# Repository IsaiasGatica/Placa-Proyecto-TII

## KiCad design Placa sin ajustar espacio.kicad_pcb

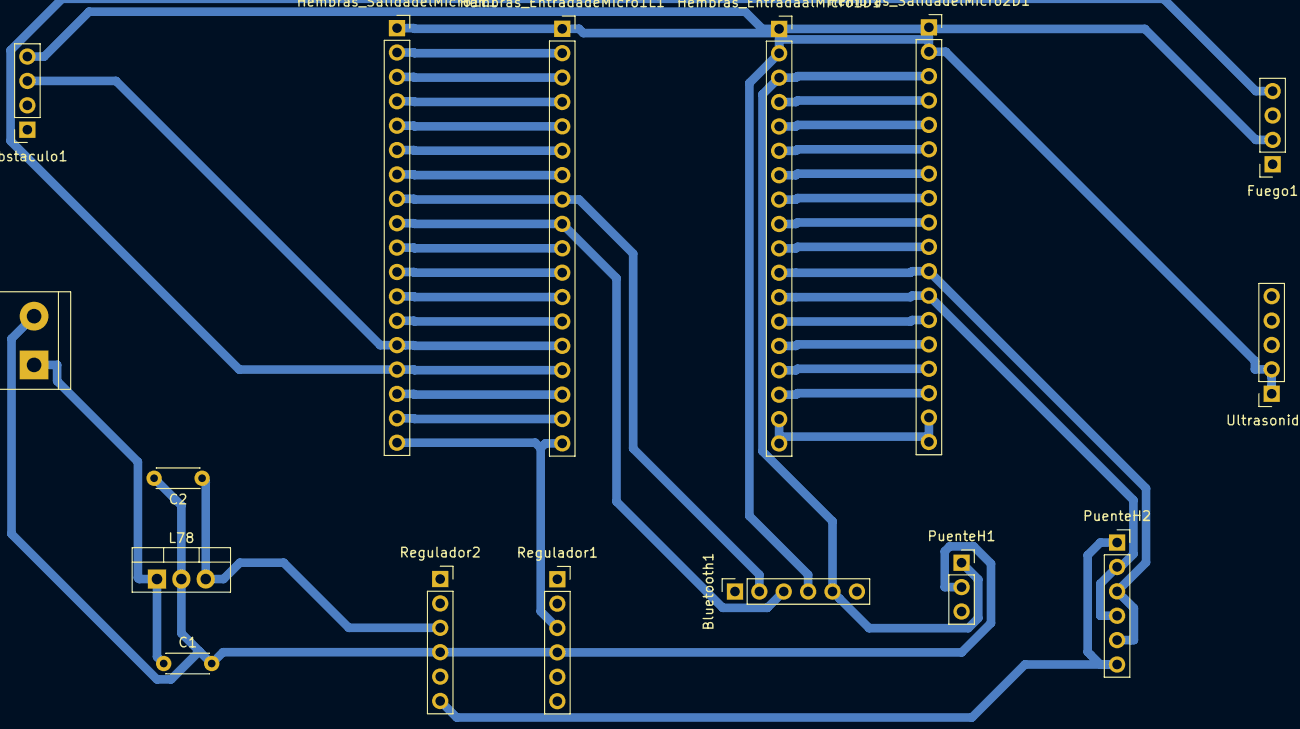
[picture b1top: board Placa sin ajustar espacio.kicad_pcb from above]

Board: 2 copper layers, 20 parts (0 on the bottom side), 34 nets.

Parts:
Alimentacion1: Screw_Terminal_01x02; TerminalBlock_bornier-2_P5.08mm
Bluetooth1: Conn_01x06_Female; PinSocket_1x06_P2.54mm_Vertical
C1: 224; C_Disc_D4.3mm_W1.9mm_P5.00mm
C2: 104; C_Disc_D4.3mm_W1.9mm_P5.00mm
Fuego1: Conn_01x04_Female; PinSocket_1x04_P2.54mm_Vertical
Hembras_EntradaalMicro1D1: Conn_01x18_Female; PinSocket_1x18_P2.54mm_Vertical
Hembras_EntradadeMicro1L1: Conn_01x18_Female; PinSocket_1x18_P2.54mm_Vertical
Hembras_SalidadelMicro1L1, Hembras_SalidadelMicro2D1: Conn_01x18_Female; PinSocket_1x18_P2.54mm_Vertical
L78: L7805; TO-220-3_Vertical
MH1, MH2, MH3, MH4: MountingHole; MountingHole_3mm
Obstaculo1: Conn_01x04_Female; PinSocket_1x04_P2.54mm_Vertical
PuenteH1: Conn_01x03_Female; PinSocket_1x03_P2.54mm_Vertical
PuenteH2: Conn_01x06_Female; PinSocket_1x06_P2.54mm_Vertical
Regulador1, Regulador2: Conn_01x06_Female; PinSocket_1x06_P2.54mm_Vertical
Ultrasonido1: Conn_01x05_Female; PinSocket_1x05_P2.54mm_Vertical

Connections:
1: Bluetooth1.3, Hembras_EntradadeMicro1L1.9, Hembras_SalidadelMicro1L1.9
2: Hembras_EntradadeMicro1L1.10, Hembras_SalidadelMicro1L1.10
3: Hembras_EntradadeMicro1L1.11, Hembras_SalidadelMicro1L1.11
4: Hembras_EntradadeMicro1L1.12, Hembras_SalidadelMicro1L1.12, Ultrasonido1.4
5: Hembras_EntradadeMicro1L1.13, Hembras_SalidadelMicro1L1.13, Ultrasonido1.3
5V(regulado): Bluetooth1.5, C2.1, Hembras_EntradaalMicro1D1.3, Hembras_SalidadelMicro2D1.3, L78.3, PuenteH1.1, Regulador2.3, Ultrasonido1.5
8: Hembras_EntradadeMicro1L1.14, Hembras_SalidadelMicro1L1.14, Obstaculo1.3
9: Fuego1.4, Hembras_EntradadeMicro1L1.15, Hembras_SalidadelMicro1L1.15
10: Hembras_EntradadeMicro1L1.16, Hembras_SalidadelMicro1L1.16
11: Hembras_EntradadeMicro1L1.17, Hembras_SalidadelMicro1L1.17
12V: Alimentacion1.1, C1.1, L78.1, PuenteH1.3
14: Hembras_EntradaalMicro1D1.16, Hembras_SalidadelMicro2D1.16
15: Hembras_EntradaalMicro1D1.15, Hembras_SalidadelMicro2D1.15
16: Hembras_EntradaalMicro1D1.14, Hembras_SalidadelMicro2D1.14
17: Hembras_EntradaalMicro1D1.13, Hembras_SalidadelMicro2D1.13, Regulador1.6
19: Hembras_EntradaalMicro1D1.12, Hembras_SalidadelMicro2D1.12, PuenteH2.2, PuenteH2.4
20: Hembras_EntradaalMicro1D1.11, Hembras_SalidadelMicro2D1.11, PuenteH2.3, PuenteH2.5
21: Hembras_EntradaalMicro1D1.10, Hembras_SalidadelMicro2D1.10
22: Hembras_EntradaalMicro1D1.9, Hembras_SalidadelMicro2D1.9
24: Hembras_EntradaalMicro1D1.8, Hembras_SalidadelMicro2D1.8
25: Hembras_EntradaalMicro1D1.7, Hembras_SalidadelMicro2D1.7
26: Hembras_EntradaalMicro1D1.6, Hembras_SalidadelMicro2D1.6
27: Hembras_EntradaalMicro1D1.5, Hembras_SalidadelMicro2D1.5
32: Hembras_EntradaalMicro1D1.4, Hembras_SalidadelMicro2D1.4
35: Hembras_EntradadeMicro1L1.2, Hembras_SalidadelMicro1L1.2
36: Hembras_EntradadeMicro1L1.3, Hembras_SalidadelMicro1L1.3
38: Hembras_EntradadeMicro1L1.4, Hembras_SalidadelMicro1L1.4
39: Hembras_EntradadeMicro1L1.5, Hembras_SalidadelMicro1L1.5
40: Hembras_EntradadeMicro1L1.6, Hembras_SalidadelMicro1L1.6
41: Hembras_EntradadeMicro1L1.7, Hembras_SalidadelMicro1L1.7
44: Bluetooth1.2, Hembras_EntradadeMicro1L1.8, Hembras_SalidadelMicro1L1.8
GND: Alimentacion1.2, Bluetooth1.4, C1.2, C2.2, Fuego1.2, Hembras_EntradaalMicro1D1.1, Hembras_EntradaalMicro1D1.2, Hembras_EntradadeMicro1L1.1, Hembras_SalidadelMicro1L1.1, Hembras_SalidadelMicro2D1.1, Hembras_SalidadelMicro2D1.2, L78.2, Obstaculo1.4, PuenteH1.2, Regulador1.4, Regulador2.4, Ultrasonido1.1, Ultrasonido1.2
PWM(Regulador): PuenteH2.1, PuenteH2.6, Regulador2.6
Vcc(u): Fuego1.3, Hembras_EntradaalMicro1D1.17, Hembras_EntradaalMicro1D1.18, Hembras_EntradadeMicro1L1.18, Hembras_SalidadelMicro1L1.18, Hembras_SalidadelMicro2D1.17, Hembras_SalidadelMicro2D1.18, Obstaculo1.2, Regulador1.3

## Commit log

2019-07-01 Ultima version de la placa
2019-07-01 Se subieron los PDF
2019-07-01 Se agrego GND del Servo
2019-07-01 Se actualizaron los PDF
